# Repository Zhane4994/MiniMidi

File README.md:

# MiniMidi

[View SCH on KiCanvas](https://kicanvas.org/?repo=https://github.com/Zhane4994/MiniMidi/blob/main/PCB/Midi-keyboard.kicad_sch)

This project, I created an Octave Synth, following a tutorial provided by Hack Club's Half-Life

This uses touch capacitive keys to output a MIDI output to my computer. Some issues I faced were getting a devboard that has enough pads for the octave keys. I fixed this by finding another devboard by waveshare, the ESP32-S3-Tiny which is a dual module component, and I had to create a custom footprint and symbol for it. 
I also faced an issue on how to create the exposed copper art on the back! I was able to fix this by just changing the slikscreen graphic to the F.Mask layer and flipping it so it's on the back mask layer.
 
# Features
 - 3 Cherry Style Switches
 - 3 SK6812 Mini E LED's
 - EC11E Rotary Encoder for Volume Control
 - 12 Key/Octave Piano Layout
 - 3 Gateron Style Hotswap Sockets
 - 2 Bourns Potentiometers
 - Dual Custom Footprints for ESP32 Board
 - Copper Exposed Art
 - Case
# Onshape Case
[Onshape](https://cad.onshape.com/documents/bcc6a2a10356ec5954083393/w/1139bc4e4e214bda93f027fe/e/de3ed0a024fbd457ad4d6f78?renderMode=0&uiState=6adece5aef25e90a8274034f)
# Ai Usage
I used ai to confirm some things such as creating my Key Ratios for white keys to black keys

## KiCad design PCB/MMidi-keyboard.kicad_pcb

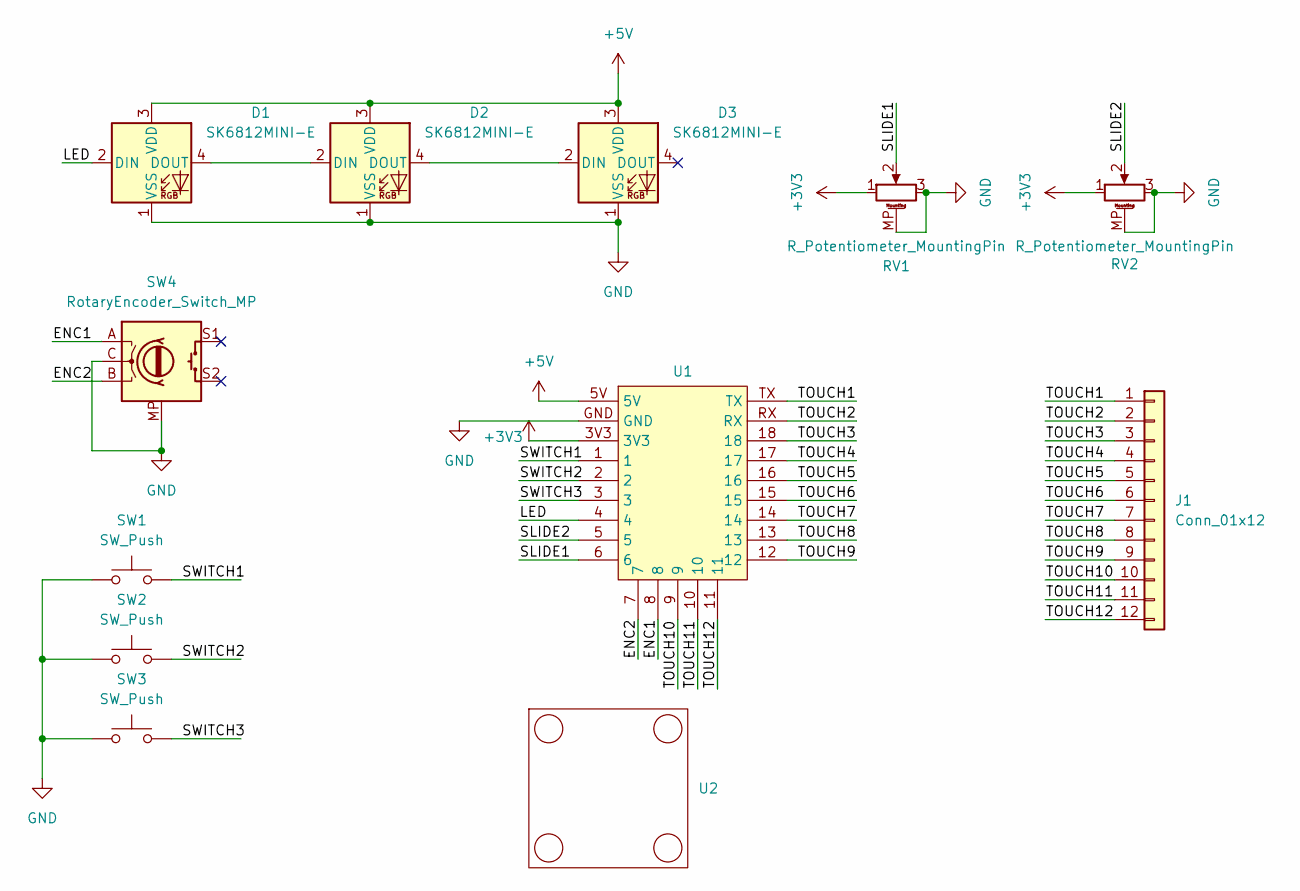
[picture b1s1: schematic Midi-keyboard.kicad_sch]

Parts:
D1, D2, D3: SK6812MINI-E; LED_SK6812MINI-E_3.2x2.8mm_P1.5mm_ReverseMount
J1: Conn_01x12; Capacitive Keys
RV1, RV2: R_Potentiometer_MountingPin; Potentiometer_Bourns_PTA1543_Single_Slide
SW1, SW2, SW3: SW_Push; SW_MX_HS_KS-2P02B01-01_1u
SW4: RotaryEncoder_Switch_MP; RotaryEncoder_Alps_EC11E-Switch_Vertical_H20mm
U1: ESP32-S3-Tiny Main
U2: ESP32-S3-Tiny USB

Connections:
+3V3: RV1.1, RV2.1, U1.3V3
+5V: D1.3 (VDD), D2.3 (VDD), D3.3 (VDD), U1.5V
/ENC1: SW4.A, U1.8
/ENC2: SW4.B, U1.7
/LED: D1.2 (DIN), U1.4
/SLIDE1: RV1.2, U1.6
/SLIDE2: RV2.2, U1.5
/SWITCH1: SW1.2, U1.1
/SWITCH2: SW2.2, U1.2
/SWITCH3: SW3.2, U1.3
/TOUCH1: J1.1, U1.TX
/TOUCH2: J1.2, U1.RX
/TOUCH3: J1.3, U1.18
/TOUCH4: J1.4, U1.17
/TOUCH5: J1.5, U1.16
/TOUCH6: J1.6, U1.15
/TOUCH7: J1.7, U1.14
/TOUCH8: J1.8, U1.13
/TOUCH9: J1.9, U1.12
/TOUCH10: J1.10, U1.9
/TOUCH11: J1.11, U1.10
/TOUCH12: J1.12, U1.11
GND: D1.1 (VSS), D2.1 (VSS), D3.1 (VSS), RV1.3, RV1.MP (MountPin), RV2.3, RV2.MP (MountPin), SW1.1, SW2.1, SW3.1, SW4.C, SW4.MP, U1.GND
unnamed: D1.4 (DOUT), D2.2 (DIN)
unnamed: D2.4 (DOUT), D3.2 (DIN)

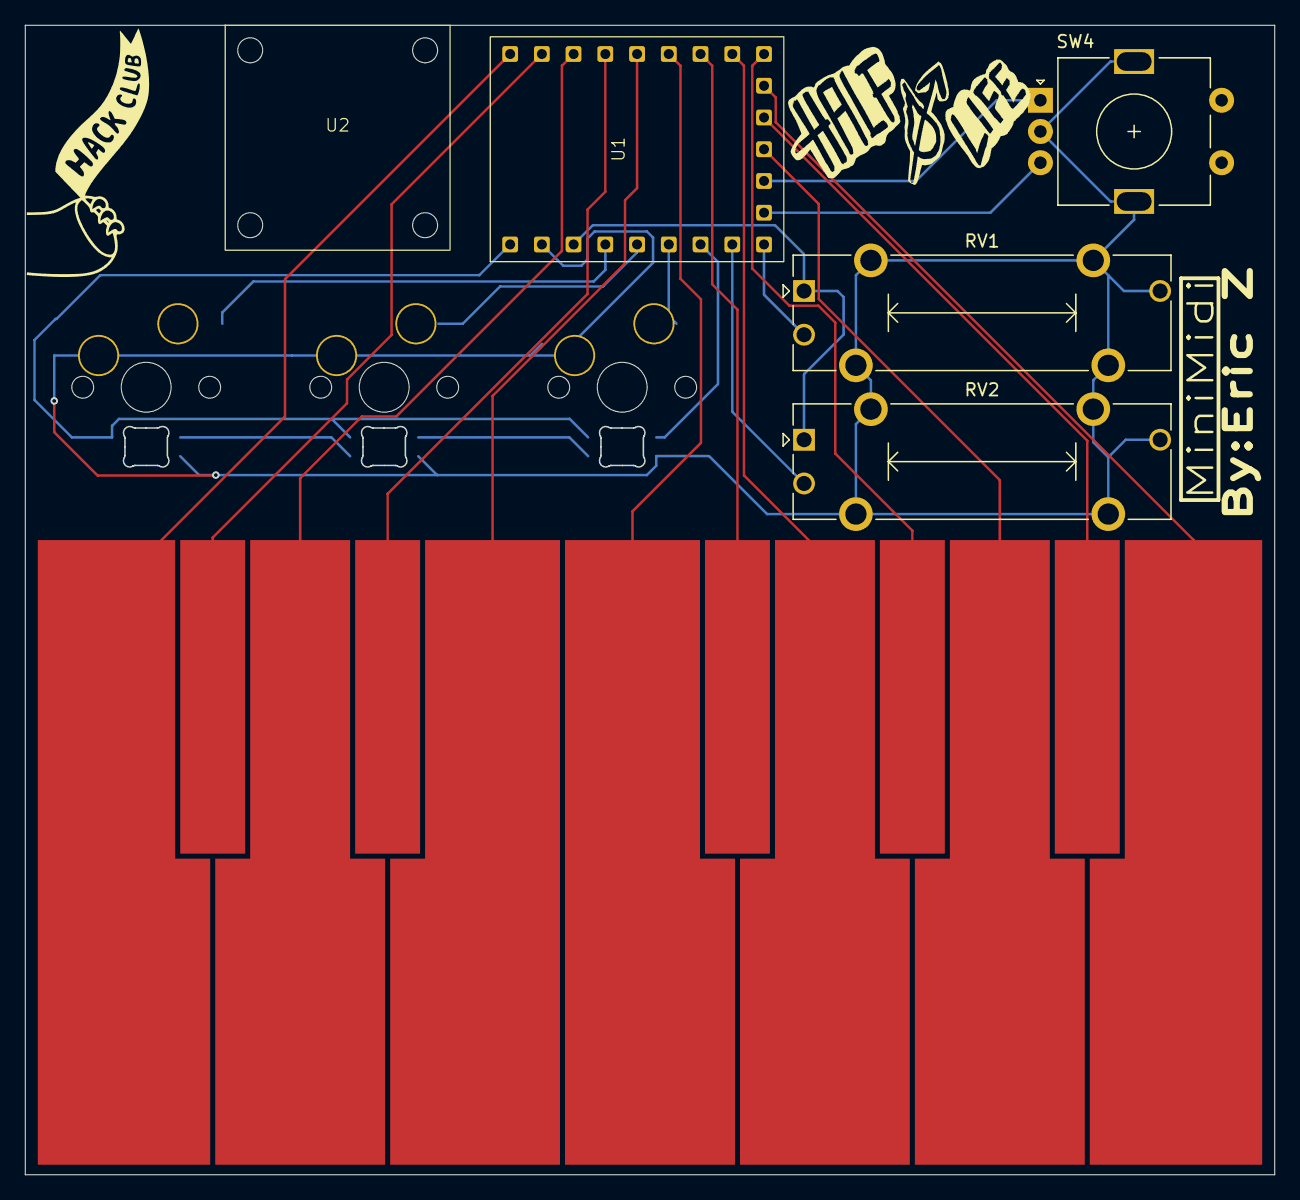
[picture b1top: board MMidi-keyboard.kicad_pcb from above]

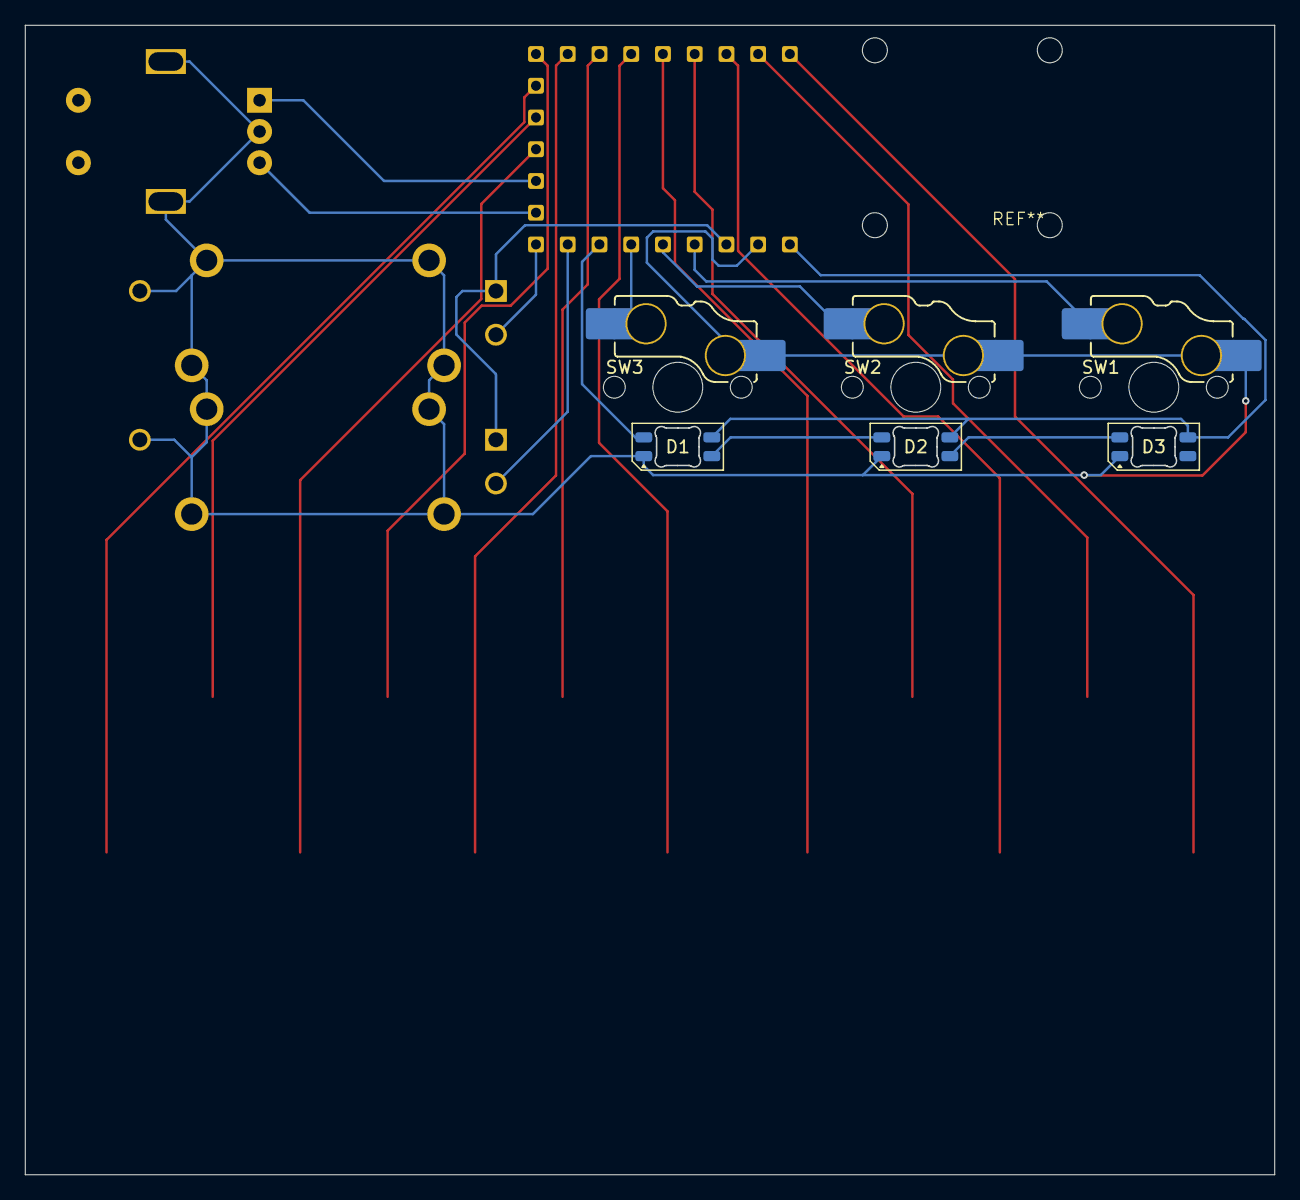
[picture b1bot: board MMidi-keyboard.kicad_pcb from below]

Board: 2 copper layers, 100.0 x 92.0 mm, 12 parts (6 on the bottom side), 25 nets.

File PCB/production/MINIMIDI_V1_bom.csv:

Designator,Footprint,Quantity,Value,LCSC Part #
"D1, D2, D3",LED_SK6812MINI-E_3.2x2.8mm_P1.5mm_ReverseMount,3,SK6812MINI-E,
J1,Capacitive Keys,1,Conn_01x12,
"RV1, RV2",Potentiometer_Bourns_PTA1543_Single_Slide,2,R_Potentiometer_MountingPin,
"SW1, SW2, SW3",SW_MX_HS_KS-2P02B01-01_1u,3,SW_Push,
SW4,RotaryEncoder_Alps_EC11E-Switch_Vertical_H20mm,1,RotaryEncoder_Switch_MP,
U1,ESP32-S3-Tiny Main,1,~,
U2,ESP32-S3-Tiny USB,1,~,
